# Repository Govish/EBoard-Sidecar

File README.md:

# EBoard Sidecar
 A circuit board for my electric longboard that controls soft power, precharge, and LEDs

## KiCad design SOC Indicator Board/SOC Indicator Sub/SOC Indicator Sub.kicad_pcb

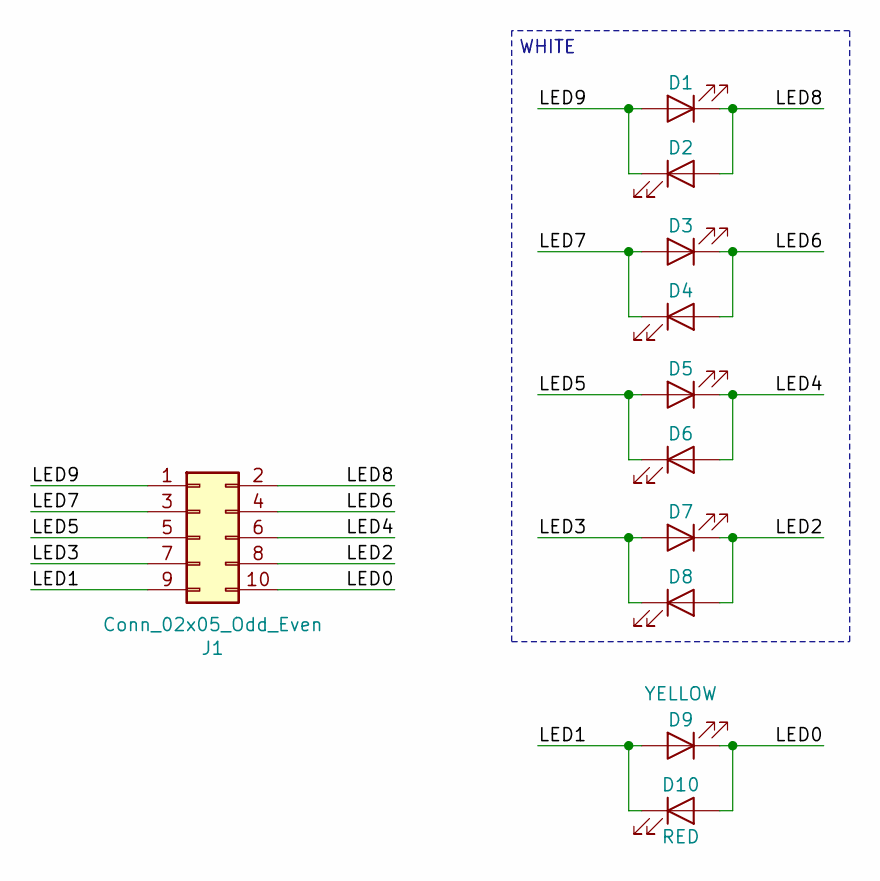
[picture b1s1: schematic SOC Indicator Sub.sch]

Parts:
D1, D2, D3, D4, D5, D6, D7, D8: WHITE; LED_D3.0mm_Clear
D9: YELLOW; LED_D3.0mm_Clear
D10: RED; LED_D3.0mm
J1: Conn_02x05_Odd_Even; PinHeader_2x05_P2.54mm_Horizontal

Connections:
/LED0: D9.1 (K), D10.2 (A), J1.10
/LED1: D9.2 (A), D10.1 (K), J1.9
/LED2: D7.1 (K), D8.2 (A), J1.8
/LED3: D7.2 (A), D8.1 (K), J1.7
/LED4: D5.1 (K), D6.2 (A), J1.6
/LED5: D5.2 (A), D6.1 (K), J1.5
/LED6: D3.1 (K), D4.2 (A), J1.4
/LED7: D3.2 (A), D4.1 (K), J1.3
/LED8: D1.1 (K), D2.2 (A), J1.2
/LED9: D1.2 (A), D2.1 (K), J1.1

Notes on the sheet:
WHITE

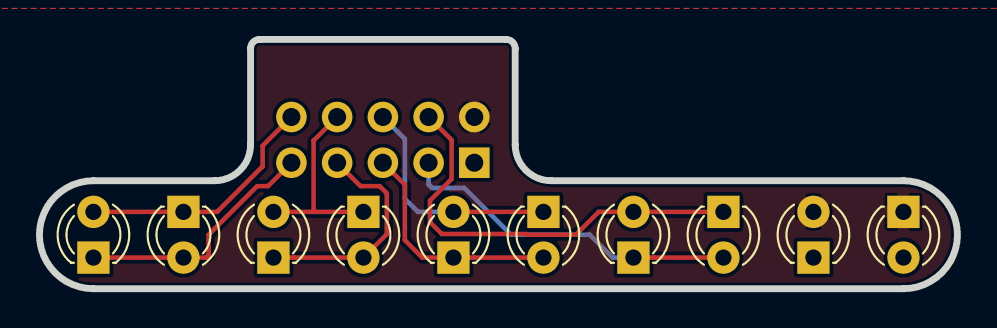
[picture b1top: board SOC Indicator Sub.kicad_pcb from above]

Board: 2 copper layers, 51.0 x 13.8 mm, 11 parts (1 on the bottom side), 10 nets.

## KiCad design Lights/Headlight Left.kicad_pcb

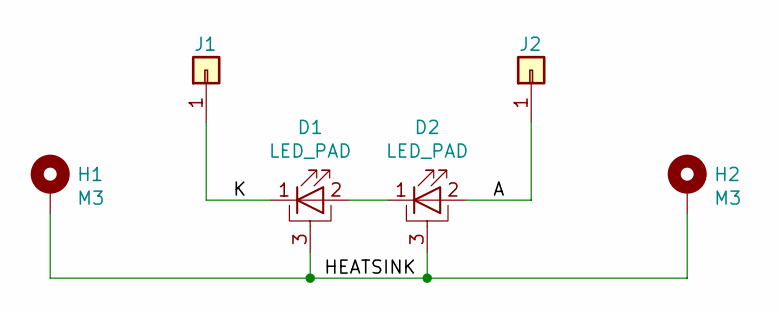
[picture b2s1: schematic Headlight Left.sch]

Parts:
D1, D2: LED_PAD; 1W_LED
H1, H2: M3; MountingHole_3.2mm_M3_Pad_Via
J1, J2: Conn_01x01; TestPoint_Keystone_5019_Minature

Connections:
/A: D2.2 (A), J2.1
/HEATSINK: D1.3 (PAD), D2.3 (PAD), H1.1, H2.1
/K: D1.1 (K), J1.1
unnamed: D1.2 (A), D2.1 (K)

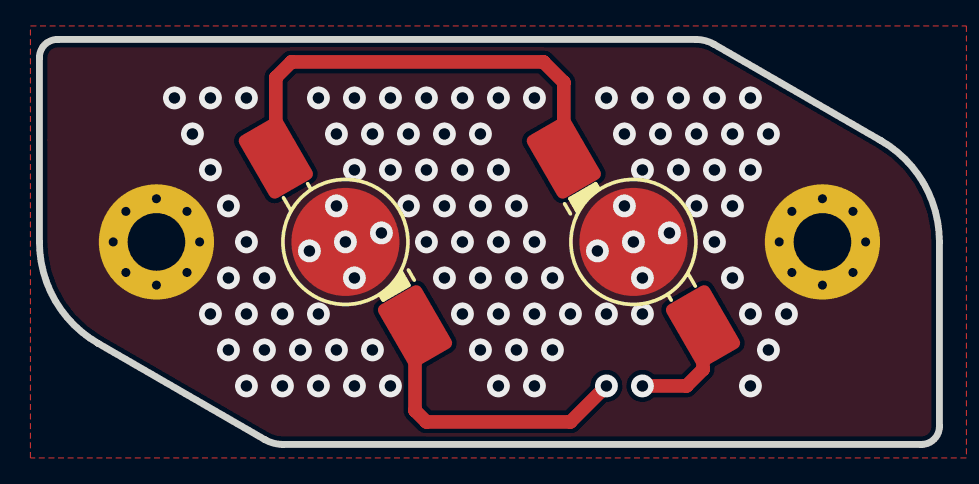
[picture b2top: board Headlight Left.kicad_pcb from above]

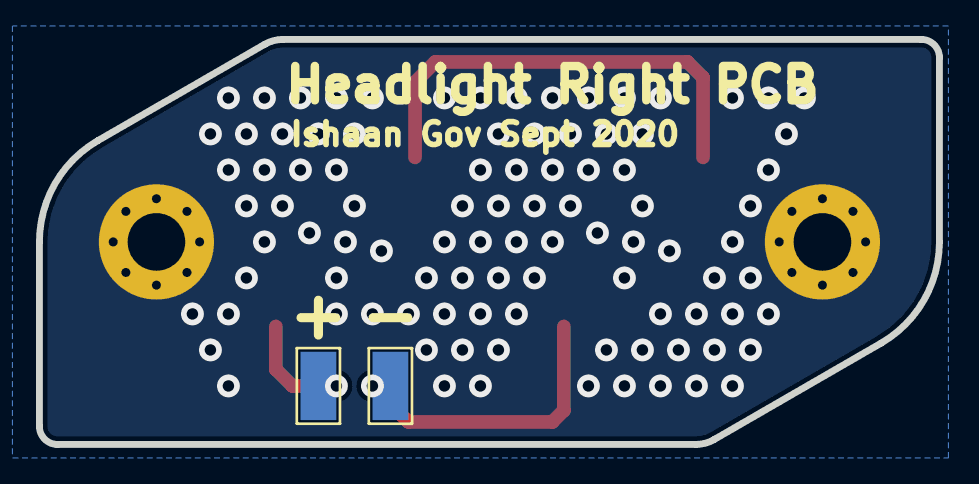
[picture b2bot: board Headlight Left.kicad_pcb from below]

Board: 2 copper layers, 50.0 x 22.5 mm, 6 parts (2 on the bottom side), 4 nets.

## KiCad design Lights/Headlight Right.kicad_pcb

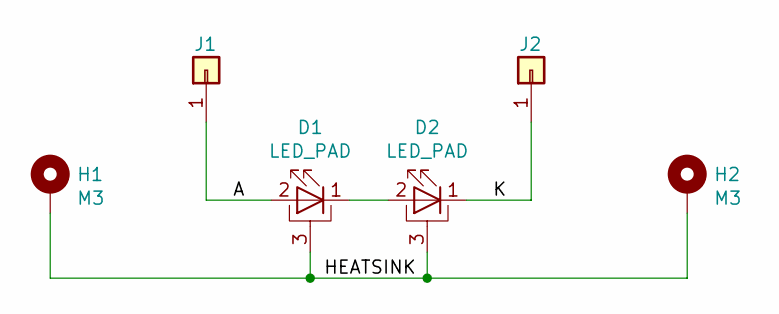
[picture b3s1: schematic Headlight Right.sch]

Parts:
D1, D2: LED_PAD; 1W_LED
H1, H2: M3; MountingHole_3.2mm_M3_Pad_Via
J1, J2: Conn_01x01; TestPoint_Keystone_5019_Minature

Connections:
/A: D1.2 (A), J1.1
/HEATSINK: D1.3 (PAD), D2.3 (PAD), H1.1, H2.1
/K: D2.1 (K), J2.1
unnamed: D1.1 (K), D2.2 (A)

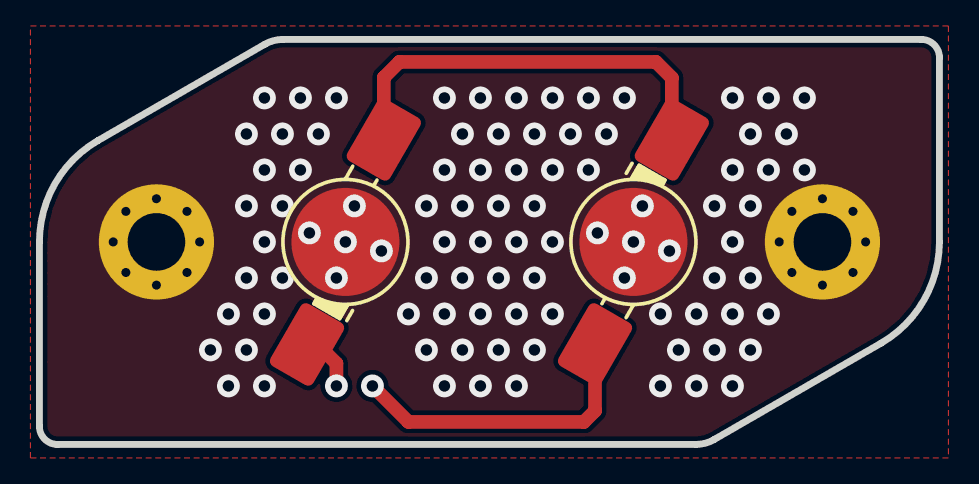
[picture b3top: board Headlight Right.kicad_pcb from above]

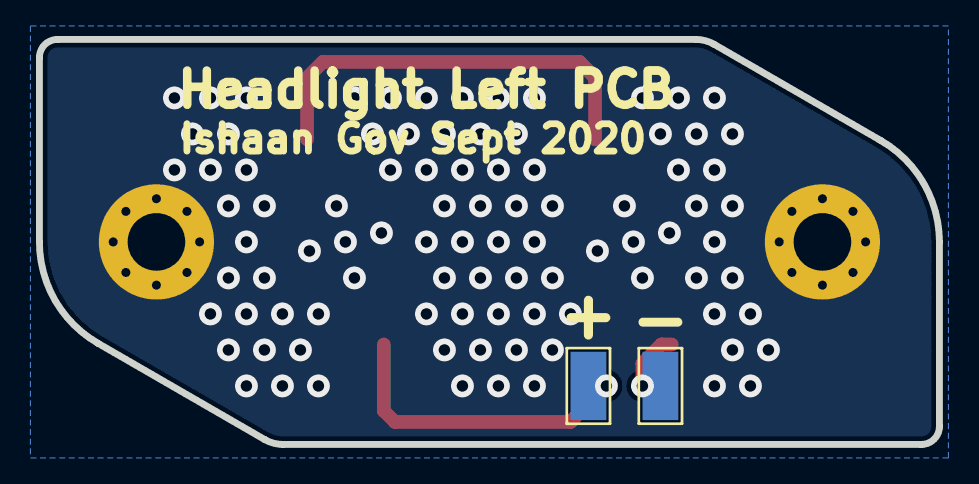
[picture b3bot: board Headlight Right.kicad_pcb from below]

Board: 2 copper layers, 50.0 x 22.5 mm, 6 parts (2 on the bottom side), 4 nets.

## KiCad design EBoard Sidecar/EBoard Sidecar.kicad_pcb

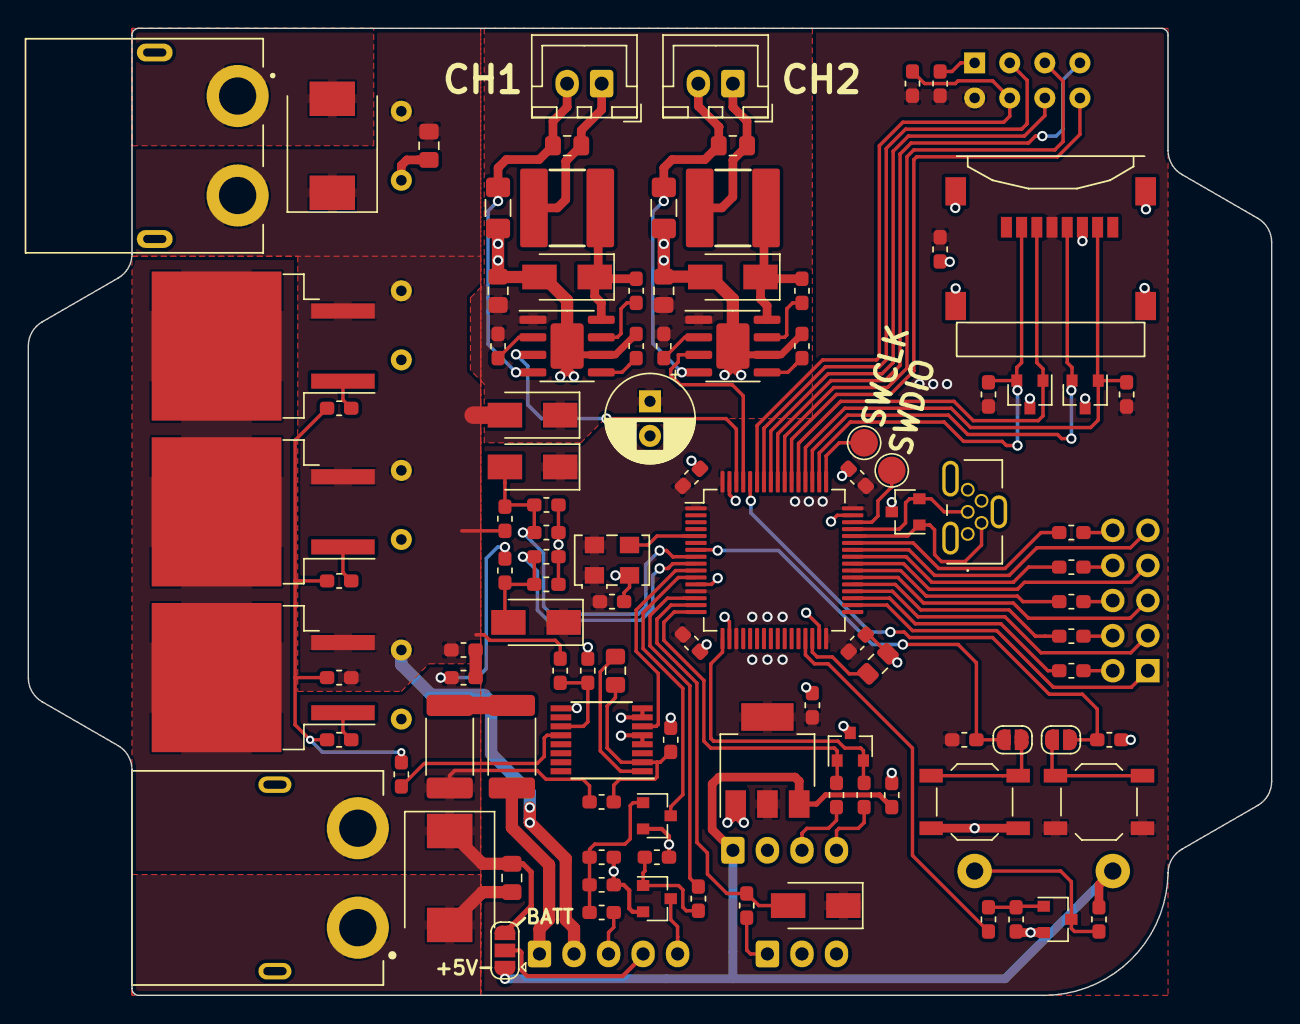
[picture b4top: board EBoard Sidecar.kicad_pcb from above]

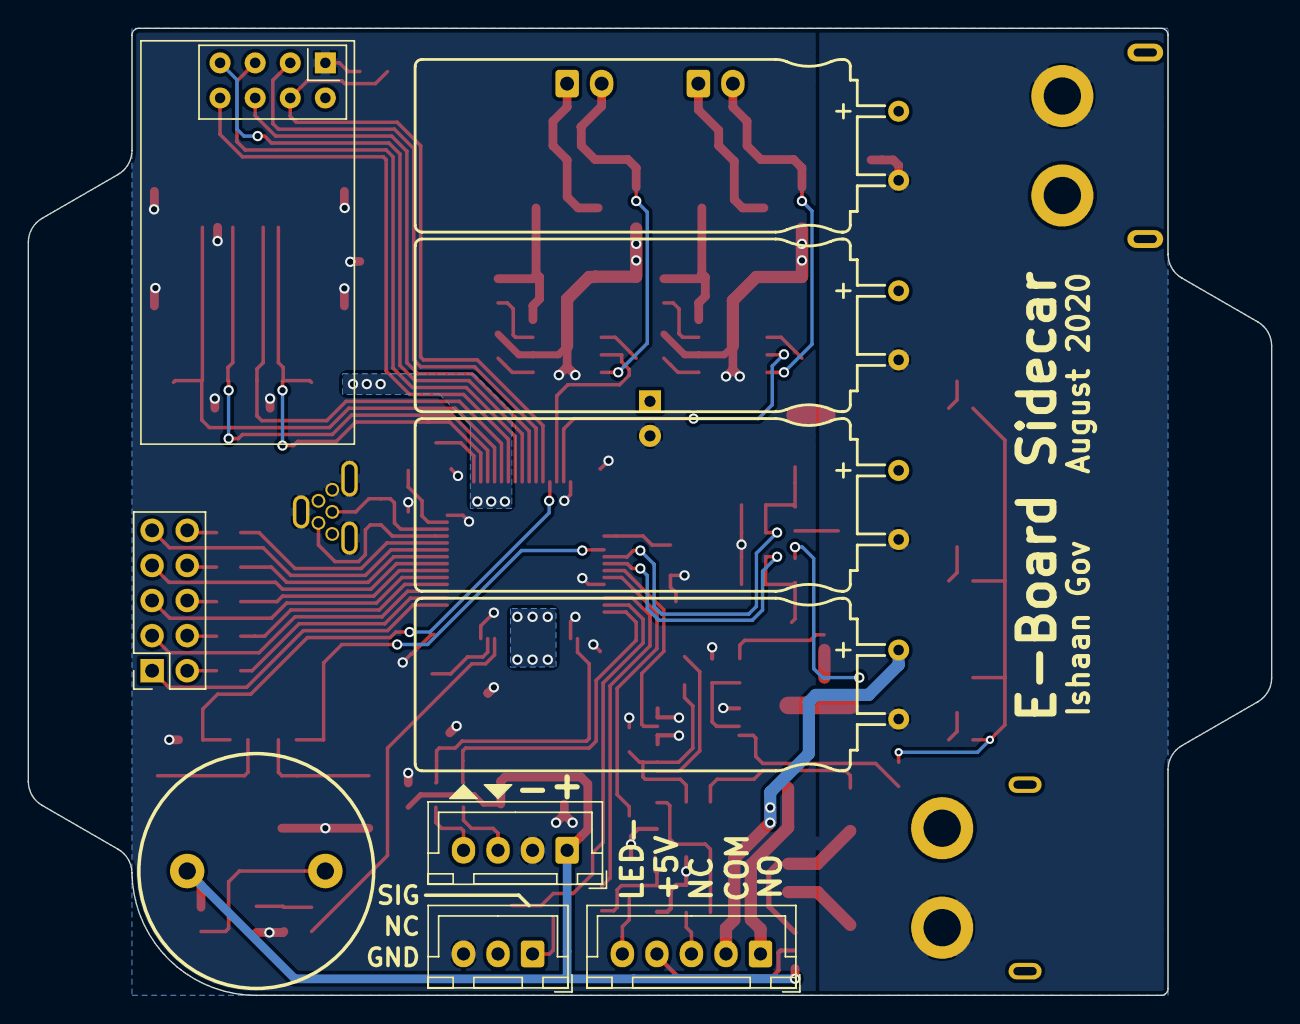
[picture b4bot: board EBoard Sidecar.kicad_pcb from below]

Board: 2 copper layers, 90.0 x 70.0 mm, 119 parts (10 on the bottom side), 85 nets.

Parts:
BZ301: ZL-YDW17075; Buzzer_10mm
C101, C108, C208, C209, C403: 1u; C_0805_2012Metric_Pad1.15x1.40mm_HandSolder
C102, C103, C301: 10u; C_0603_1608Metric_Pad1.05x0.95mm_HandSolder
C104, C105, C106, C107: 1000u; UHW1H102MHD
C201: 47u; CP_Radial_D6.3mm_P2.50mm
C202, C203, C304: 4u7; C_0805_2012Metric_Pad1.15x1.40mm_HandSolder
C204, C205, C206, C207, C302, C303, C305, C306, C307, C308, C404, C405: 100n; C_0603_1608Metric_Pad1.05x0.95mm_HandSolder
C309, C401, C402, C406, C407: 10n; C_0603_1608Metric_Pad1.05x0.95mm_HandSolder
D101, D102: SMCJ45A; D_SMC
D201, D202, D203, D301, D401, D402: SS16; D_SMA
D302, D303, D304, D305: CESD3V3AP; SOT-23
H101, H102, H103, H104: Zip Tie; ZipTie-5mm
J101: Conn_XT; XT60PW-M
J102, J103: Conn_01x02; JST_XH_B2B-XH-A_1x02_P2.50mm_Vertical
J104: Conn_01x05; JST_XH_B5B-XH-A_1x05_P2.50mm_Vertical
J105: Conn_XT; XT60PW-F
J301: Conn_01x03; JST_XH_B3B-XH-A_1x03_P2.50mm_Vertical
J302: Conn_01x04; JST_XH_B4B-XH-A_1x04_P2.50mm_Vertical
J303: Micro_SD_Card; MOLEX_47219-2001
J304: USB_B_Mini; TE_1734753-1
J305: Conn_02x05_Odd_Even; PinSocket_2x05_P2.54mm_Vertical
JP301, JP302: SolderJumper_2_Open; SolderJumper-2_P1.3mm_Open_RoundedPad1.0x1.5mm
JP401: SolderJumper_3_Open; SolderJumper-3_P1.3mm_Open_RoundedPad1.0x1.5mm
L201, L202: 100u; SMNR6028
Q301, Q302, Q303: 2N7002; SOT-23
Q401, Q402, Q403: HY3606; TO-263-2
R201, R202: 47k; R_0603_1608Metric_Pad1.05x0.95mm_HandSolder
R203, R204: 0.68R; R_1206_3216Metric_Pad1.42x1.75mm_HandSolder
R301, R310: 1K; R_0603_1608Metric_Pad1.05x0.95mm_HandSolder
R302, R303, R405, R406, R407: 27R; R_0603_1608Metric_Pad1.05x0.95mm_HandSolder
R304, R305, R306, R307, R308, R402, R414: 10K; R_0603_1608Metric_Pad1.05x0.95mm_HandSolder
R309, R312, R314, R404, R408, R411: 100R; R_0603_1608Metric_Pad1.05x0.95mm_HandSolder
R311, R313, R319, R401, R413: 100K; R_0603_1608Metric_Pad1.05x0.95mm_HandSolder
R315, R316, R317, R318: 68R; R_0603_1608Metric_Pad1.05x0.95mm_HandSolder
R320: 240K; R_0603_1608Metric_Pad1.05x0.95mm_HandSolder
R409, R412: 33R 1W; R_2512_6332Metric_Pad1.52x3.35mm_HandSolder
R410: 10M; R_0603_1608Metric_Pad1.05x0.95mm_HandSolder
SW301, SW302: SW_Push; SW_SPST_TL3342
TP301, TP302: TestPoint; TestPoint_Pad_D2.0mm
U101: AZ1117-3.3; SOT-223-3_TabPin2
U201, U202: A6211; SOIC-8-1EP_3.9x4.9mm_P1.27mm_EP2.41x3.3mm
U301: NRF24L01_Breakout; nRF24L01_Breakout
U302: STM32F401RETx; LQFP-64_10x10mm_P0.5mm
U401: BQ76200; TSSOP-16_4.4x5mm_P0.65mm
X301: 8MHz; Oscillator_SMD_EuroQuartz_XO53-4Pin_5.0x3.2mm

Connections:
+3V3: C103.1, C301.1, C302.1, C303.1, C305.1, C306.1, C307.1, C308.1, D301.1, D401.1, D402.1, J303.4, R304.2, R305.2, R306.2, R308.2, SW302.1, U101.2, U301.2, U302.1, U302.13, U302.19, U302.32, U302.48, U302.64, X301.1, X301.4
+5V: BZ301.1, C102.1, J302.1, JP401.1, R310.2, U101.3
/COM: C104.1, C105.1, C106.1, C107.1, C108.1, C405.2, D102.1, D201.2, J104.2, J105.+, Q401.3, Q402.3, Q403.3, R410.1, R411.2, R413.2
/Digital/BATT+: C101.1, C404.1, D101.1, J101.+, JP401.3, Q401.2, Q402.2, Q403.2, R401.2, R404.2, R409.2
/Digital/BATT_SENSE: C401.1, D401.2, R401.1, R402.2, U302.9
/Digital/BUZZER: R309.1, U302.29
/Digital/CC_CHAN_1: U201.3, U302.62
/Digital/CC_CHAN_2: U202.3, U302.61
/Digital/FROM_VESC: D302.2, R303.1, U302.17
/Digital/LED0: R314.2, U302.35
/Digital/LED1: J305.1, U302.34
/Digital/LED2: R315.2, U302.37
/Digital/LED3: J305.3, U302.36
/Digital/LED4: R316.2, U302.39
/Digital/LED5: J305.5, U302.38
/Digital/LED6: R317.2, U302.41
/Digital/LED7: J305.7, U302.40
/Digital/LED8: R318.1, U302.43
/Digital/LED9: J305.9, U302.42
/Digital/PB_IN: Q302.3, U302.11
/Digital/PB_LED: R312.1, U302.14
/Digital/RADIO_CE: U301.3, U302.58
/Digital/RADIO_CS: R304.1, U301.4, U302.59
/Digital/RADIO_IRQ: U301.8, U302.54
/Digital/RADIO_MISO: U301.7, U302.56
/Digital/RADIO_MOSI: U301.6, U302.57
/Digital/RADIO_SCK: U301.5, U302.55
/Digital/RC_IN: D301.2, R301.1, U302.15
/Digital/SD_CS: D303.2, J303.2, R305.1, U302.50
/Digital/SD_MISO: D304.1, J303.7, R306.1, U302.52
/Digital/SD_MOSI: D303.1, J303.3, U302.53
/Digital/SD_SCK: D304.2, J303.5, U302.51
/Digital/SWCLK: TP302.1, U302.49
/Digital/SWDIO: TP301.1, U302.46
/Digital/SYS_SENSE: C407.1, D402.2, R413.1, R414.2, U302.8
/Digital/TO_VESC: D302.1, R302.2, U302.16
/LED Drivers/CC_VCC: C201.1, C202.1, C203.1, D201.1, R201.1, R202.1, U201.1, U202.1
/LED Drivers/LED_1+: C208.1, J102.1, L201.2
/LED Drivers/LED_1-: C208.2, J102.2, R203.1, U201.4
/LED Drivers/LED_2+: C209.1, J103.1, L202.2
/LED Drivers/LED_2-: C209.2, J103.2, R204.1, U202.4
/LED+: J104.4, JP401.2
/LED-: J104.5, Q303.3
/NC: J104.3, R320.1
/NO: J104.1, R412.1
/Power Stage/DSG_EN: U302.10, U401.6
GND: C101.2, C102.2, C103.2, C104.2, C105.2, C106.2, C107.2, C108.2, C201.2, C202.2, C203.2, C204.2, C205.2, C301.2, C302.2, C303.2, C304.2, C305.2, C306.2, C307.2, C308.2, C309.2, C401.2, C402.2, C406.2, C407.2, D101.2, D102.2, D202.2, D203.2, D302.3, D303.3, D304.3, D305.3, J101.-, J105.-, J301.3, J302.2, J303.6, J303.9, J304.5, J304.6, Q301.2, Q302.2, Q303.2, R203.2, R204.2, R307.1, R311.1, R313.1, R319.1, R402.1, R414.1, SW301.1, U101.1, U201.6, U201.9, U202.6, U202.9, U301.1, U302.12, U302.18, U302.31, U302.47, U302.63, U401.4, U401.5, U401.7, U401.8, U401.9, X301.2
unnamed: BZ301.2, Q301.3, R310.1
unnamed: C204.1, U201.5
unnamed: C205.1, U202.5
unnamed: C206.1, U201.7
unnamed: C206.2, D202.1, L201.1, U201.8
unnamed: C207.1, U202.7
unnamed: C207.2, D203.1, L202.1, U202.8
unnamed: C304.1, U302.30
unnamed: C309.1, Q302.1, R319.2, R320.2
unnamed: C402.1, C403.1, R404.1, U401.2
unnamed: C403.2, U401.1
unnamed: C404.2, C405.1
unnamed: C406.1, R411.1, U401.11
unnamed: D305.1, J304.2, U302.44
unnamed: D305.2, J304.3, U302.45
unnamed: J301.1, R301.2
unnamed: J302.3, R302.1
unnamed: J302.4, R303.2
unnamed: J305.2, R314.1
unnamed: J305.4, R315.1
unnamed: J305.6, R316.1
unnamed: J305.8, R317.1
unnamed: J305.10, R318.2
unnamed: JP301.1, SW301.2
unnamed: JP301.2, R308.1, U302.7
unnamed: JP302.1, SW302.2
unnamed: JP302.2, R307.2, U302.60
unnamed: Q301.1, R309.2, R311.2
unnamed: Q303.1, R312.2, R313.2
unnamed: Q401.1, R405.2
unnamed: Q402.1, R406.2
unnamed: Q403.1, R407.2
unnamed: R201.2, U201.2
unnamed: R202.2, U202.2
unnamed: R405.1, R406.1, R407.1, R408.2, R410.2
unnamed: R408.1, U401.12
unnamed: R409.1, R412.2
unnamed: U302.5, X301.3

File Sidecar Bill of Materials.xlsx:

E-Board Sidecar Bill of Materials
LAST UPDATED 8/18/2020
Reference Number | Package | Quantity | Price @Break | Total Price | Value | Manufacturer | Part Number | Supplier (LCSC) P/N | Notes for Substitution | Qty on Hand
BZ301, | Buzzer_10mm | 1 | 0.63 | 0.63 | ZL-YDW17075 | ZLFY | ZL-YDW17075-4005PA-10 | C219733 | 90+ dbA at 5V | 0
C101, C108, C208, C209, C403, | 0805 | 5 | 0.10400000000000001 | 0.52 | 1u | CTCC | TCC0805X7R105K500DTS | C344178 | 1u, 50V, X5R or Better | 0
C102, C103, C301, | 0603 | 3 | 0.21333333333333335 | 0.64 | 10u | Samsung Electro-Mechanics | CL10A106KP8NNNC | C19702 | 10u, 10V, X5R or Better | 0
C105, C106, C107, C104, | D12.5mm_P5mm | 4 | 0.79 | 3.16 | 1000u | Nichicon | UHW1H102MHD | C250864 | 1000uF, 50V+, 3A+ ripple | 0
C201, | D6.3mm_P2.50mm | 1 | 0.19 | 0.19 | 47u | Aihua Group | SPZ1HM470E08O00RAXXX | C122243 | Same or greater value, 50V+ | 0
C202, C203, C304, | 0805 | 3 | 0.13666666666666666 | 0.41 | 4u7 | Samsung Electro-Mechanics | CL21A475KBQNNNE | C98192 | 4.7u, 50V, X5R or Better | 0
C204, C206, C205, C207, C302, C305, C307, C308, C303, C306, C404, C405, | 0603 | 12 | 1.3333333333333334E-2 | 0.16 | 100n | CCTC | TCC0603X7R104K500CT | C282519 | 100n, 50V, X5R or Better | 50
C309, C406, C402, C401, C407, | 0603 | 5 | 5.6000000000000008E-2 | 0.28000000000000003 | 10n | Prosperity Dielectrics | FN18X103K500PSG | C525264 | 10n, 50V, X5R or Better | 0
D101, D102, | SMC | 2 | 0.22500000000000001 | 0.45 | SMCJ45A | Shandong Jingdao Microelectronics | SMCJ45A | C438113 | 37-45V Reverse Standoff, 1000W+ | 0
D202, D203, D201, D301, D401, D402, | SMA | 6 | 9.3333333333333338E-2 | 0.56000000000000005 | SS16 | Shandong Jingdao Microelectronics | SS16 | C353240 | 40+V, 350mA | 0
D304, D303, D302, D305, | SOT-23 | 4 | 0.1 | 0.4 | CESD3V3AP | Changjiang Electronics Tech | CESD3V3AP | C70435 | 3.3V Reverse Standoff | 0
J101, | - | 1 | 0.69 | 0.69 | XT60PW-M | Changzhou Amass Electronics | XT60PW-M | C98732 | - | 0
J102, J103, | 2P-2.5mm | 2 | 0.28999999999999998 | 0.57999999999999996 | Conn_01x02 | JST Sales America | B2B-XH-A(LF)(SN) | C158012 | - | 0 | C144401 for Housing P/N | C140573 for Housing Pin P/N
J104, | 5P-2.5mm | 1 | 0.34 | 0.34 | Conn_01x05 | JST Sales America | B5B-XH-A(LF)(SN) | C157991 | - | 1 | C144404 for Housing P/N | C140573 for Housing Pin P/N
J105, | - | 1 | 0.65 | 0.65 | XT60PW-F | Changzhou Amass Electronics | XT60PW-F | C428722 | - | 0
J301, | 3P-2.5mm | 1 | 0.43 | 0.43 | Conn_01x03 | JST Sales America | B3B-XH-A(LF)(SN) | C144394 | - | 0 | C144402 for Housing P/N | C140573 for Housing Pin P/N
J302, | 4P-2.5mm | 1 | 0.49 | 0.49 | Conn_01x04 | JST Sales America | B4B-XH-A(LF)(SN) | C144395 | - | 2 | C144403 for Housing P/N | C140573 for Housing Pin P/N
J303, | - | 1 | 0.53 | 0.53 | Micro_SD_Card | Molex | 472192001 | C164170 | - | 0
J304, | - | 1 | 0.91 | 0.91 | USB_B_Mini | TE Connectivity | 1734753-1 | C305989 | - | 0
J305, | 10P-2x5-0.1" | 1 | 0.52 | 0.52 | Conn_02x05_Odd_Even | Boom Precision Electronics | C5665 | C5665 | IDC10, 0.1" Spacing | 1
L201, L202, | 6060 | 2 | 0.22500000000000001 | 0.45 | 100u | Shun Xiang Nuo Elec | SMNR6028-101MT | C266434 | 100uH, 350mA+ | 0
Q301, Q302, Q303, | SOT-23-3 | 3 | 0.24 | 0.72 | 2N7002 | Leshan Radio Co | L2N7002SLT1G | C250818 | 60V, ~100mA | 0
Q401, Q402, Q403, | TO-263-2 | 3 | 0.56000000000000005 | 1.6800000000000002 | HY3606 | HUAYI | HY3606B | C133396 | <5mOhm, 50+ Vds | 0
R201, R202, | 0603 | 2 | 0.06 | 0.12 | 47K | Uniroyal Electronics | 0603WAF4702T5E | C25819 | 47K, 1% | 0
R203, R204, | 1206 | 2 | 0.27 | 0.54 | 0.68R | Walsin Tech Corp | WW12WR680FTL | C383883 | >0.1W, Low TCR | 0
R302, R303, R405, R406, R407, | 0603 | 5 | 2.4E-2 | 0.12 | 27R | Uniroyal Electronics | 0603WAF270JT5E | C25190 | 1% or better
R305, R306, R304, R308, R307, R402, R414, | 0603 | 7 | 1.4285714285714287E-2 | 0.1 | 10K | Uniroyal Electronics | 0603WAF1002T5E | C25804 | 1% or better
R309, R312, R318, R408, R411, R404, | 0603 | 6 | 0.02 | 0.12 | 100R | Uniroyal Electronics | 0603WAF1000T5E | C22775 | 1% or better
R310, R301, | 0603 | 2 | 0.05 | 0.1 | 1K | Guangdong Fenghua Advanced Tech | RS-03K1001FT | C115325 | 1% or better
R311, R319, R313, R401, R413, | 0603 | 5 | 2.6000000000000002E-2 | 0.13 | 100K | Uniroyal Electronics | 0603WAF1003T5E | C25803 | 1% or better | 0
R317, R316, R315, R314, | 0603 | 4 | 0.03 | 0.12 | 68R | Uniroyal Electronics | 0603WAF680JT5E | C27592 | 1% or better
R320, | 0603 | 1 | 0.12 | 0.12 | 240K | Uniroyal Electronics | 0603WAF2403T5E | C4197 | 1% or better
R409, R412, | 2512 | 2 | 0.21 | 0.42 | 33R 1W | Uniroyal Electronics | 25121WJ0330T4E | C473038 | 33R, 1W | 0
R410, | 0603 | 1 | 0.15 | 0.15 | 10M | Uniroyal Electronics | 0603WAF1005T5E | C7250 | 1% or better
SW301, SW302, | - | 2 | 0.185 | 0.37 | SW_Push | SHOU HAN | TS5220A | C412370 | - | 0
U101, | SOT-223-2 | 1 | 0.39 | 0.39 | AZ1117-3.3 | Diodes Inc. | AZ1117CH-3.3TRG1 | C92102 | 1117 pinout, <1.7v dropout, 500mA | 0
U201, U202, | SOIC-8 EP | 2 | 0.93 | 1.86 | A6211 | Allegro Microsystems | A6211GLJTR-T | C150827 |  | 0
U301, | - | 1 | 6.69 | 6.69 | NRF24L01_Breakout | Generic/Nordic Semiconductor | NRF24L01 Module | Amazon | Generic THT Module | 0
U302, | LQFP64 | 1 | 2.64 | 2.64 | STM32F401RETx | STMicroelectronics | STM32F401RET6 | C116978 | - | 0
U401, | TSSOP16 | 1 | 1.49 | 1.49 | BQ76200 | Texas Instruments | BQ76200PWR | C216213 | - | 0
X301, | 5032 | 1 | 0.54 | 0.54 | 8MHz | Yangxing Tech | OT50328MJBA4SL | C669089 | 8MHz, 5032 | 0
 |  | BOM Total |  | 31.410000000000007

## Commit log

2020-08-27 Basically finishing everything off
2021-01-10 Adding gerber files
